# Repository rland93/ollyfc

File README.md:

# ollyfc
A small rust-embedded flight computer. RTIC, FrSky protocols, and STM32F4 hardware.

Board bring-up progress:

- [x] Buzzer
- [x] HDC 1080 Humidity and Temperature Sensor
- [x] BMI088 IMU
- [x] PCA9865 PWM Controller
- [x] Servo Channels from 5v power rail
- [x] FrSky SBUS External Reciever
- [x] BMP388 Pressure Sensor
- [x] LIS3MDL Magnetometer
- [x] FrSky SBUS 
- [ ] U-blox NEO m8n GPS unit
- [ ] NPA 730B differential pressure sensor
- [x] W25Q External Flash Memory
- [ ] UART for holybro 915MHz telemetry radio

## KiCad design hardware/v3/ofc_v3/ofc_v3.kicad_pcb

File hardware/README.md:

# OllyFC Hardware

We have hardware!

Schematics:

+ [V1 Schematic (PDF Link)](v1/ollyfc_v1_schematic.pdf)

# v1

V1 is manufactured by JLCPCB. The final project files (including JLCPCB Part Numbers / Bill of Materials) is in the v1/production folder. Images:

3D View (Tilted)

3D View (Top)

Traces (Top)

Traces (Bottom)

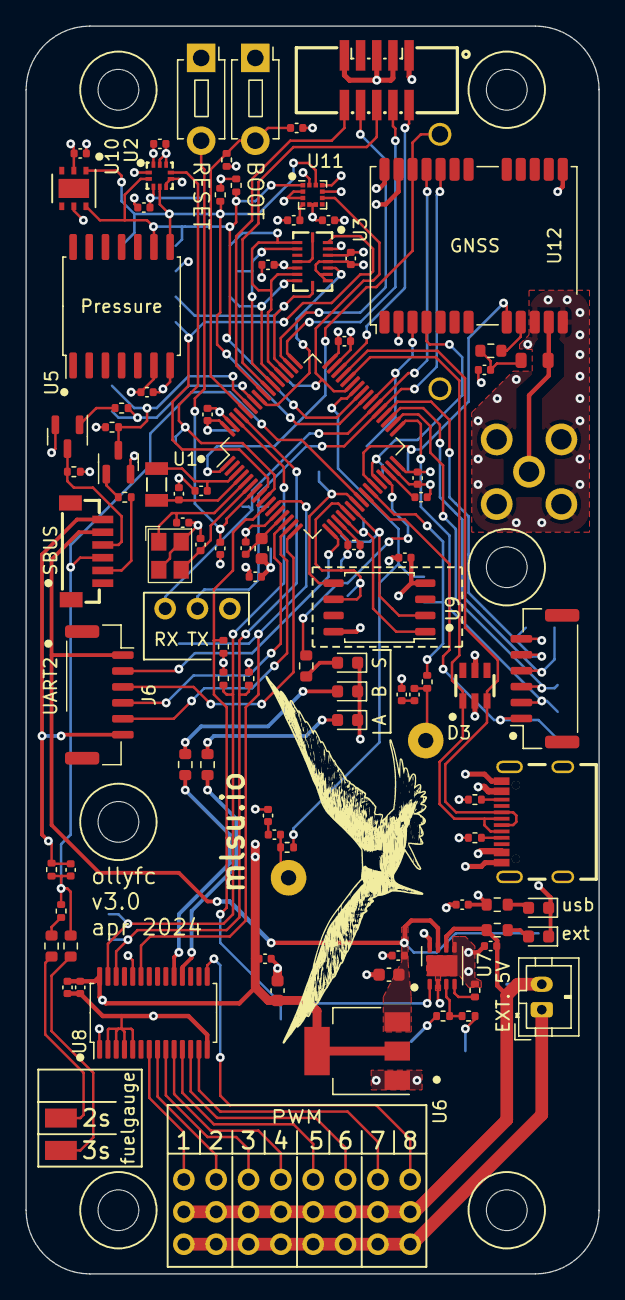
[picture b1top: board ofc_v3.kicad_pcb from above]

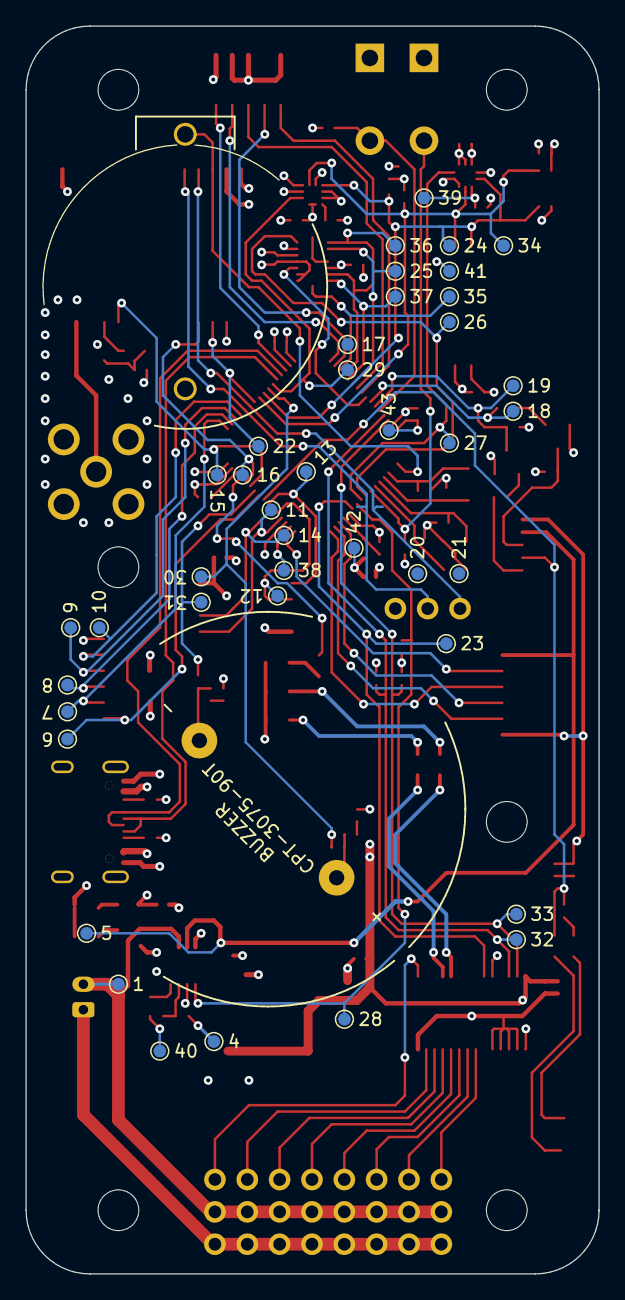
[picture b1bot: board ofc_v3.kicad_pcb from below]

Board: 4 copper layers, 45.0 x 98.0 mm, 150 parts (43 on the bottom side), 94 nets.

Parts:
BT1: 2998; BH-25C-1_ADM
BZ1: 102-CPT-3075-90T-ND; XDCR_CPT-3075-90T
C1, C2, C3, C4, C5, C8, C9, C11, C12, C13, C14, C15, C16, C19, C20, C22, C23, C24, C27, C28, C29, C30, C31, C32, C35, C36: 100n; C_0402_1005Metric
C6, C7: 10p; C_0402_1005Metric
C10, C21, C33: 4.7u; C_0402_1005Metric
C17, C18: 4.7u; C_0603_1608Metric
C25, C26: 33p; C_0402_1005Metric
C34: 10n; C_0402_1005Metric
CN1: 20021521-00010T1LF; IDC-SMD_10P-P1.27_X1270WVS-2X05B-6TV01
CN2: BM06B-SRSS-TBT(LF)(SN); CONN-SMD_BM06B-SRSS-TBT-LF-SN
D1, D7: 19-213/Y2C-CQ2R2L/3T(CY); LED_0603_1608Metric
D2, D4, D6: KT-0603R; LED_0603_1608Metric
D3: SRV05-4_C7420376; SOT-23-6_L2.9-W1.6-P0.95-LS2.8-BL-1
FB1: GZ1608D601TF; L_0603_1608Metric
H1, H2, H3, H4, H5, H6: DIN912; MountingHole_3.2mm_M3
J1: Conn_01x02; JST_PH_B2B-PH-K_1x02_P2.00mm_Vertical
J2, J3, J4: Conn_01x09; PinHeader_1x08_P2.54mm_Vertical
J5: GNSS_RF; SMA-TH_KH-SMA-KE-Z
J6, J7: Conn_01x06; JST_GH_SM06B-GHS-TB_1x06-1MP_P1.25mm_Horizontal
J8: Conn_01x03; PinHeader_1x03_P2.54mm_Vertical
L1: 27nH; L_0805_2012Metric
Q2, Q3: MMBT3904; SOT-23
R1, R2, R3, R4, R6, R12, R13, R14, R15, R16, R17, R25: 5.1K; R_0402_1005Metric
R5, R9, R24, R26, R27: 150; R_0603_1608Metric
R7, R8, R18, R19: 1.5K; R_0402_1005Metric
R10, R11, R21: 1K; R_0402_1005Metric
R20: 3K; R_0603_1608Metric
R22: 10; R_0603_1608Metric
R23: 7.5K; R_0603_1608Metric
SW1, SW2: SW_RST; SW_PUSH_1P1T_6x3.5mm_H4.3_APEM_MJTP1243
TP1, TP4, TP5, TP6, TP7, TP8, TP9, TP10, TP11, TP12, TP13, TP14, TP15, TP16, TP17, TP18, TP19, TP20, TP21, TP22, TP23, TP24, TP25, TP26, TP27, TP28, TP29, TP30, TP31, TP32, TP33, TP34, TP35, TP36, TP37, TP38, TP39, TP40, TP41, TP42, TP43: TestPoint; TestPoint_Pad_D1.0mm
TP2, TP3: TestPoint; TestPoint_Pad_2.0x2.0mm
U1: STM32F401RCTx; LQFP-64_10x10mm_P0.5mm
U2: BMP388; SENSORM-SMD_BMP388
U3: BMI088; LGA-16_L4.5-W3.0-P0.50-BL
U4: GT-USB-7010ASV; USB-C-SMD_G-SWITCH_GT-USB-7010ASV
U5: NPA-730B-10WD; SOIC-14W_7.5x9mm_P1.27mm
U6: AMS1117-3.3; SOT-223
U7: TPS2113ADRBR; VSON-8-1EP_3x3mm_P0.65mm_EP1.65x2.4mm
U8: PCA9685PW; TSSOP-28_4.4x9.7mm_P0.65mm
U9: W25Q128JVS; SOIC-8_5.23x5.23mm_P1.27mm
U10: HDC1080; Texas_PWSON-N6
U11: LIS3MDL; LGA-12_2x2mm_P0.5mm
U12: NEO-M8N; ublox_NEO
X1: X322512MSB4SI; OSC-SMD_4P-L3.2-W2.5-BL
X2: Q13FC1350000400; FC-135R_L3.2-W1.5

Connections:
5VIN: C17.1, C35.1, CN2.5, J6.1, TP5.1, U6.3 (VIN), U7.7 (OUT)
+3.3VA: C9.1, FB1.2, U1.13 (VREF+)
+3V3: C1.1, C2.1, C3.1, C4.1, C8.2, C10.1, C11.1, C12.1, C13.1, C14.1, C15.1, C18.1, C21.1, C22.1, C23.1, C27.1, C28.1, C36.1, CN1.1, FB1.1, R1.2, R2.2, R6.1, R12.2, R13.2, R14.2, R17.2, SW2.1, TP41.1, TP42.1, TP43.1, U1.19 (VDD), U1.32 (VDD), U1.48 (VDD), U1.64 (VDD), U2.1 (VDDIO), U2.5 (SDO), U2.6 (CSB), U2.10 (VDD), U3.3 (VDD), U3.11 (VDDIO), U5.7 (VDD), U6.2 (VOUT), U6.4 (VOUT), U8.1 (A0), U8.28 (VDD), U9.8 (VCC), U10.5 (VCC), U11.5 (Vdd), U11.6 (Vdd_IO), U11.10 (~CS), U12.2 (D_SEL), U12.23 (VCC)
/STATUS_LED: R24.1, U1.29 (PB10)
/io-sensors/2s: R20.1, TP2.1
/io-sensors/3s: R23.1, TP3.1
/io-sensors/rf_in: J5.1 (In), L1.2, U12.11 (RF_IN)
/io-sensors/s_port: CN2.4, Q2.3 (C), R14.1
/io-sensors/sbus_out: CN2.2, R16.2
/io-sensors/vcc_rf: R22.2, U12.9 (VCC_RF)
/power/ILIM: R10.1, U7.4 (ILIM)
/power/LED1: R26.1, U8.18 (LED11)
/power/LED2: R27.1, U8.19 (LED12)
/power/VSNS: R7.2, R8.1, U7.3 (VSNS)
/power/ch1: J2.1, U8.7 (LED1)
/power/ch2: J2.2, U8.8 (LED2)
/power/ch3: J2.3, U8.9 (LED3)
/power/ch4: J2.4, U8.10 (LED4)
/power/ch5: J2.5, U8.11 (LED5)
/power/ch6: J2.6, U8.12 (LED6)
/power/ch7: J2.7, U8.13 (LED7)
/power/ch8: J2.8, U8.15 (LED8)
ACC_CS: TP25.1, U1.54 (PD2), U3.14 (CSB1)
AIN_2: C24.1, CN2.3, R18.2, R19.1, R23.2, U1.24 (PC4)
AUX: J7.1, TP6.1, U1.25 (PC5)
BOOT0: C8.1, R25.2, SW2.2, U1.60 (BOOT0)
BUZZ+: R11.1, TP30.1, U1.42 (PA9)
BUZZ-: R21.1, TP31.1, U1.26 (PB0)
GND: BT1.2 (-), C1.2, C2.2, C3.2, C4.2, C5.2, C6.1, C7.1, C9.2, C10.2, C11.2, C12.2, C13.2, C14.2, C15.2, C16.2, C17.2, C18.2, C19.2, C21.2, C22.2, C23.2, C24.2, C25.1, C26.1, C27.2, C28.2, C29.2, C30.2, C32.2, C33.2, C34.2, C35.2, C36.2, CN1.3, CN1.5, CN1.9, CN2.6, D1.1 (K), D2.1 (K), D3.2, D4.1 (K), D6.1 (K), D7.1 (K), J1.1, J4.1, J4.2, J4.3, J4.4, J4.5, J4.6, J4.7, J4.8, J5.2 (Ext), J6.6, J7.6, J8.1, Q2.2 (E), Q3.2 (E), R3.1, R4.1, R8.2, R10.2, R19.2, R25.1, SW1.1, TP38.1, TP39.1, TP40.1, U1.12 (VSSA), U1.18 (VSS), U1.31 (VSS), U1.47 (VSS), U1.63 (VSS), U2.3 (VSS), U2.8 (VSS), U2.9 (VSS), U3.2 (NC), U3.4 (GNDA), U3.6 (GNDIO), U3.7 (PS), U4.1 (SHELL), U4.2 (SHELL), U4.3 (SHELL), U4.4 (SHELL), U4.A1B12 (GND), U4.B1A12 (GND), U5.6 (VSS), U6.1 (GND), U7.2 (~EN), U7.5 (GND), U7.9 (EP), U8.2 (A1), U8.3 (A2), U8.4 (A3), U8.5 (A4), U8.14 (VSS), U8.24 (A5), U9.4 (GND), U10.2 (GND), U11.2 (GND), U11.3 (GND), U11.9 (SDO/SA1), U11.12 (GND), U12.10 (GND), U12.12 (GND), U12.13 (GND), U12.24 (GND), X1.2 (GND), X1.4 (GND)
GNSS_INT: TP16.1, U1.28 (PB2), U12.4 (EXTINT)
GNSS_RESET: TP15.1, U1.27 (PB1), U12.8 (~RESET)
GYRO_CS: TP17.1, U1.57 (PB5), U3.5 (CSB2)
HSE_IN: C7.2, U1.5 (PH0), X1.1 (OSC1)
HSE_OUT: C6.2, U1.6 (PH1), X1.3 (OSC2)
I2C1_SCL: R12.1, TP32.1, U1.61 (PB8), U8.26 (SCL)
I2C1_SDA: R13.1, TP33.1, U1.62 (PB9), U8.27 (SDA)
I2C3_SCL: R2.1, TP24.1, U1.41 (PA8), U2.2 (SCK), U5.9 (SCL), U10.6 (SCL), U11.1 (SCL/SPC)
I2C3_SDA: R1.1, TP34.1, U1.40 (PC9), U2.4 (SDI), U5.8 (SCL), U10.1 (SDA), U11.11 (SDA/SDI/SDO)
IMU_DRDY: TP26.1, U1.8 (PC0), U3.1 (INT2)
JTCK_SWCLK: CN1.4, U1.49 (PA14)
JTDI: CN1.8, U1.50 (PA15)
JTDO_SWO: CN1.6, U1.55 (PB3)
JTMS_SWDIO: CN1.2, U1.46 (PA13)
JTRST: CN1.10, U1.56 (PB4)
MAG_DRDY: TP29.1, U1.43 (PA10), U11.8 (DRDY)
NRST: C5.1, SW1.2, U1.7 (NRST)
unnamed: BZ1.N, C31.1, R21.2
unnamed: BZ1.P, C20.1, R11.2
unnamed: C20.2, C30.1
unnamed: C31.2, C32.1
unnamed: C34.1, L1.1, R22.1
unnamed: D1.2 (A), R9.2
unnamed: D2.2 (A), R5.2
unnamed: D4.2 (A), R24.2
unnamed: D6.2 (A), R27.2
unnamed: D7.2 (A), R26.2
unnamed: Q2.1 (B), R15.2
unnamed: Q3.1 (B), R16.1
unnamed: R18.1, R20.2
unnamed: C26.2, U1.3 (PC14), X2.1
unnamed: C25.2, U1.4 (PC15), X2.2
unnamed: C33.1, U1.30 (VCAP1)
unnamed: U3.12 (INT3), U3.16 (INT1)
unnamed: R3.2, U4.A5 (CC1)
unnamed: R4.2, U4.B5 (CC2)
unnamed: C29.1, U11.4 (C1)
PRES_DRDY: TP27.1, U1.9 (PC1), U2.7 (INT)
PWR_STATE: R6.2, TP28.1, U1.10 (PC2), U7.1 (STAT)
SERVO_EN: TP23.1, U1.11 (PC3), U8.23 (~OE)
SPI1_MISO: TP14.1, U1.22 (PA6), U9.2 (DO(IO1))
SPI1_MOSI: TP13.1, U1.23 (PA7), U9.5 (DI(IO0))
SPI1_NSS: TP11.1, U1.20 (PA4), U9.1 (~CS)
SPI1_SCK: TP12.1, U1.21 (PA5), U9.6 (CLK)
SPI2_MISO: J7.4, TP9.1, U1.35 (PB14)
SPI2_MOSI: J7.5, TP10.1, U1.36 (PB15)
SPI2_NSS: J7.2, TP7.1, U1.33 (PB12)
SPI2_SCK: J7.3, TP8.1, U1.34 (PB13)
SPI3_MISO: TP36.1, U1.52 (PC11), U3.10 (SDO2), U3.15 (SDO1)
SPI3_MOSI: TP37.1, U1.53 (PC12), U3.9 (SDA/SDI)
SPI3_SCK: TP35.1, U1.51 (PC10), U3.8 (SCL/SCK)
TIMEPULSE: TP22.1, U1.39 (PC8), U12.3 (TIMEPULSE)
USART1_RX: Q3.3 (C), R17.1, TP19.1, U1.59 (PB7)
USART1_TX: R15.1, TP18.1, U1.58 (PB6)
USART2_CTS: J6.4, U1.14 (PA0)
USART2_RTS: J6.5, U1.15 (PA1)
USART2_RX: J6.2, U1.17 (PA3)
USART2_TX: J6.3, U1.16 (PA2)
USART6_RX: J8.3, TP21.1, U1.38 (PC7), U12.21 (RXD/SPI_MOSI)
USART6_TX: J8.2, TP20.1, U1.37 (PC6), U12.20 (TXD/SPI_MISO)
USBD+: D3.3, U1.45 (PA12), U4.A6 (DP1), U4.B6 (DP2)
USBD-: D3.1, U1.44 (PA11), U4.A7 (DN1), U4.B7 (DN2)
VBAT: BT1.1 (+), U1.1 (VBAT), U12.22 (V_BCKP)
VBUS: C16.1, D3.5, R5.1, R7.1, TP4.1, U4.A4B9 (VBUS), U4.B4A9 (VBUS), U7.8 (IN1)
VIN_EXT: C19.1, J1.2, J3.1, J3.2, J3.3, J3.4, J3.5, J3.6, J3.7, J3.8, R9.1, TP1.1, U7.6 (IN2)

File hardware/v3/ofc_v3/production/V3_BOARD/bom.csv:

Designator,Footprint,Quantity,Value,LCSC Part #
BT1,BH-25C-1_ADM,1,2998,DNP
BZ1,XDCR_CPT-3075-90T,1,102-CPT-3075-90T-ND,DNP
"C1, C11, C12, C13, C14, C15, C16, C19, C2, C20, C22, C23, C24, C27, C28, C29, C3, C30, C31, C32, C35, C36, C4, C5, C8, C9",0402,26,100n,C1525
"C10, C21, C33",0402,3,4.7u,C23733
"C17, C18",0603,2,4.7u,C19666
"C25, C26",0402,2,33p,C1562
C34,0402,1,10n,C15195
"C6, C7",0402,2,10p,C32949
CN1,IDC-SMD_10P-P1.27_X1270WVS-2X05B-6TV01,1,20021521-00010T1LF,C2972785
CN2,CONN-SMD_BM06B-SRSS-TBT-LF-SN,1,BM06B-SRSS-TBT(LF)(SN),C495540
"D1, D7",0603,2,19-213/Y2C-CQ2R2L/3T(CY),C72038
"D2, D4, D6",0603,3,KT-0603R,C2286
D3,SOT-23-6_L2.9-W1.6-P0.95-LS2.8-BL-1,1,SRV05-4_C7420376,C7420376
FB1,0603,1,GZ1608D601TF,C1002
"H1, H2, H3, H4, H5, H6",MountingHole_3.2mm_M3,6,DIN912,DNP
J1,JST_PH_B2B-PH-K_1x02_P2.00mm_Vertical,1,Conn_01x02,DNP
"J2, J3, J4",PinHeader_1x08_P2.54mm_Vertical,3,Conn_01x09,DNP
J5,SMA-TH_KH-SMA-KE-Z,1,GNSS_RF,DNP
"J6, J7",JST_GH_SM06B-GHS-TB_1x06-1MP_P1.25mm_Horizontal,2,Conn_01x06,C133065
J8,PinHeader_1x03_P2.54mm_Vertical,1,Conn_01x03,DNP
L1,0805,1,27nH,C98992
"Q2, Q3",SOT-23,2,MMBT3904,C20526
"R1, R12, R13, R2, R25, R3, R4, R6",0402,8,5.1K,C25905
"R10, R11, R21",0402,3,1K,C11702
"R14, R15, R16, R17",0402,4,5.1K,C25905
"R18, R19",0402,2,1.5K,C25867
R20,0603,1,3K,C4211
R22,0603,1,10,C22859
R23,0603,1,7.5K,C23234
"R24, R26, R27, R5, R9",0603,5,150,C22808
"R7, R8",0402,2,1.5K,C25867
"SW1, SW2",SW_PUSH_1P1T_6x3.5mm_H4.3_APEM_MJTP1243,2,SW_RST,DNP
"TP1, TP10, TP11, TP12, TP13, TP14, TP15, TP16, TP17, TP18, TP19, TP20, TP21, TP22, TP23, TP24, TP25, TP26, TP27, TP28, TP29, TP30, TP31, TP32, TP33, TP34, TP35, TP36, TP37, TP38, TP39, TP4, TP40, TP41, TP42, TP43, TP5, TP6, TP7, TP8, TP9",TestPoint_Pad_D1.0mm,41,TestPoint,
"TP2, TP3",TestPoint_Pad_2.0x2.0mm,2,TestPoint,DNP
U1,LQFP-64_10x10mm_P0.5mm,1,STM32F401RCTx,C74524
U10,Texas_PWSON-N6,1,HDC1080,C82227
U11,LGA-12_2x2mm_P0.5mm,1,LIS3MDL,C478483
U12,ublox_NEO,1,NEO-M8N,DNP
U2,SENSORM-SMD_BMP388,1,BMP388,C779278
U3,LGA-16_L4.5-W3.0-P0.50-BL,1,BMI088,C194919
U4,USB-C-SMD_G-SWITCH_GT-USB-7010ASV,1,GT-USB-7010ASV,C2988369
U5,SOIC-14W_7.5x9mm_P1.27mm,1,NPA-730B-10WD,DNP
U6,SOT-223,1,AMS1117-3.3,C6186
U7,VSON-8-1EP_3x3mm_P0.65mm_EP1.65x2.4mm,1,TPS2113ADRBR,C354512
U8,TSSOP-28_4.4x9.7mm_P0.65mm,1,PCA9685PW,C2678753
U9,SOIC-8_5.23x5.23mm_P1.27mm,1,W25Q128JVS,DNP
X1,OSC-SMD_4P-L3.2-W2.5-BL,1,X322512MSB4SI,C9002
X2,FC-135R_L3.2-W1.5,1,Q13FC1350000400,C32346

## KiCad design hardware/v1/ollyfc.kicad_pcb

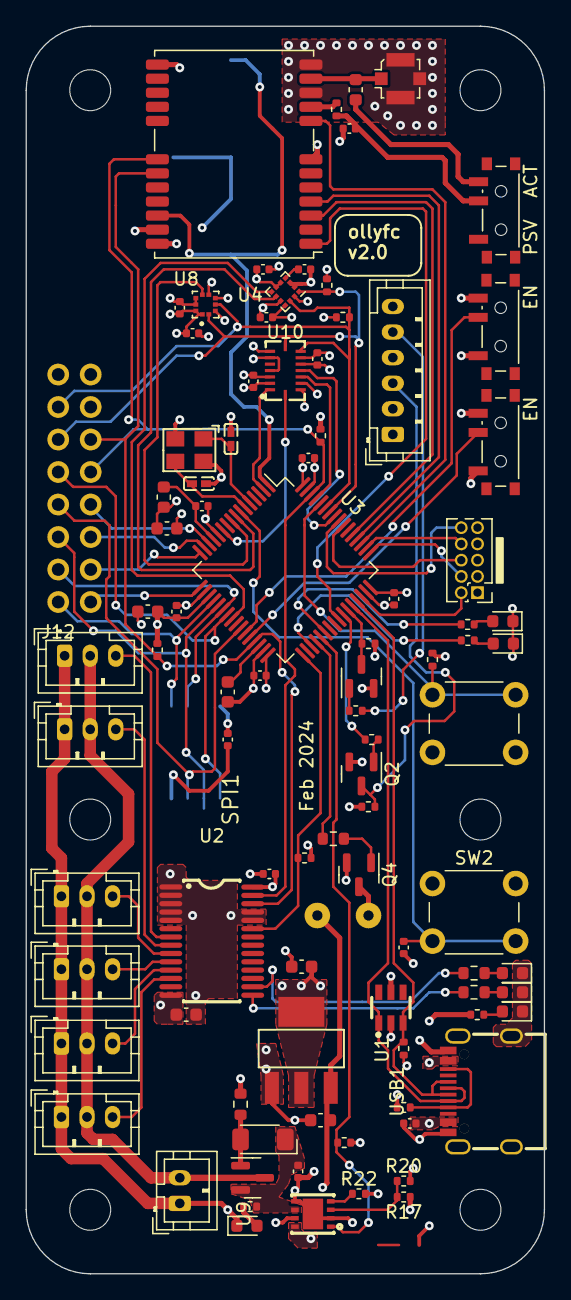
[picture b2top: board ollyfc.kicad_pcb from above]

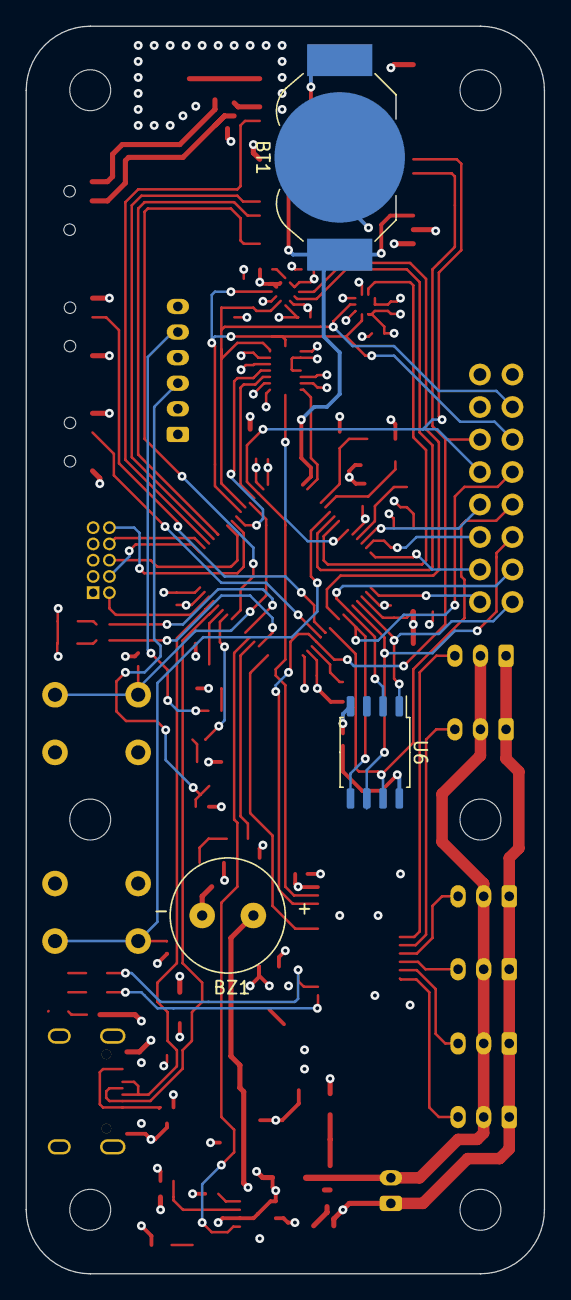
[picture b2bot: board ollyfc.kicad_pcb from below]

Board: 4 copper layers, 40.5 x 97.5 mm, 101 parts (3 on the bottom side), 82 nets.

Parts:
BT1: Battery_Cell; BatteryHolder_LINX_BAT-HLD-012-SMT
BZ1: CMT-9648-85T; XDCR_CMT-9648-85T
C1, C7, C8, C18, C19, C23: 4u7; C_0603_1608Metric
C2, C3, C4, C5, C6, C11, C12, C13, C14, C15, C16, C17, C20, C21, C24, C25: 100n; C_0402_1005Metric
C9, C10: 12pF; C0402
C22: 1u; C_0402_1005Metric
C26: 10n; C_0402_1005Metric
D1, D3, D4, D6: STATUS; LED_0603_1608Metric
D2: EXT_PWR_IND; LED_0603_1608Metric
D5: ZMM5V6-M; D_MiniMELF
D7: USB_IND; LED_0603_1608Metric
D8: SRV05-4_C7420376; SOT-23-6_L2.9-W1.6-P0.95-LS2.8-BL-1
FB1: GZ1608D601TF; L_0603_1608Metric
H1, H2, H3, H4, H5, H6: MountingHole; MountingHole_3.2mm_M3
J1: Conn_01x06; JST_PH_B6B-PH-K_1x06_P2.00mm_Vertical
J2: Conn_01x02; JST_PH_B2B-PH-K_1x02_P2.00mm_Vertical
J3, J6, J7, J9, J10, J11: Conn_01x03; JST_PH_B3B-PH-K_1x03_P2.00mm_Vertical
J5: Conn_02x05_Odd_Even; PinHeader_2x05_P1.27mm_Vertical
J8: Conn_Coaxial; U.FL_Molex_MCRF_73412-0110_Vertical
J12: Conn_01x08; PinHeader_1x08_P2.54mm_Vertical
J13: Conn_01x04; PinHeader_1x08_P2.54mm_Vertical
L1: L_Small; L_0603_1608Metric
Q1: AO3401A; SOT-23
Q2, Q3, Q4: MMBT3904; SOT-23
R1, R2, R3, R4, R5, R8, R9, R12, R15, R21, R23, R25: 5K1; R_0402_1005Metric
R6, R7, R10, R11, R16, R17, R20: 1K5; R_0402_1005Metric
R13, R14, R18, R26: 680; R_0603_1608Metric
R19: 10; R_0402_1005Metric
R22: 680; R_0402_1005Metric
SW2, SW3: SW_Push; SW_PUSH_6mm
SW4, SW5, SW6: MODE1; SW_SPDT_PCM12
U1: AMS1117-3.3; SOT-223-3_L6.5-W3.4-P2.30-LS7.0-BR
U2: PCA9685PW,118; TSSOP-28_L9.7-W4.4-P0.65-LS6.4-TL
U3: STM32F411RETx; LQFP-64_10x10mm_P0.5mm
U4: LIS3MDL; LGA-12_2x2mm_P0.5mm
U6: W25Q128JVS; SOIC-8_5.23x5.23mm_P1.27mm
U7: BMP388; BoschSensortec-BMP-388_PQFN50P200X200X80-10N
U8: NEO-M8N; ublox_NEO
U9: TPS2113ADRBR; SON-8_L3.0-W3.0-P0.65-LS3.0-BL-EP
U10: BMI088; LGA-16_L4.5-W3.0-P0.50-BL
USB1: USB-TYPE-C-018; USB-C_SMD-TYPE-C-31-M-12
X1: X322516MLB4SI; OSC-SMD_4P-L3.2-W2.5-BL

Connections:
5VIN: BZ1.P (-), C23.1, U1.3 (VIN), U9.7 (OUT)
+3.3VA: C6.1, FB1.1, U3.13 (VDDA)
+3V3: C1.1, C2.1, C3.1, C4.1, C5.1, C7.1, C12.1, C13.1, C14.1, C15.1, C16.2, C17.1, C18.1, C19.1, C21.1, C22.1, FB1.2, J1.2, J5.1, J13.1, R1.1, R4.2, R5.2, R7.1, R8.1, R9.1, R12.1, R25.1, SW3.2, SW4.3 (C), SW5.3 (C), U1.2 (VOUT), U1.4 (VOUT), U2.14 (VSS), U2.28 (VDD), U3.19 (VDD), U3.32 (VDD), U3.48 (VDD), U3.64 (VDD), U4.5 (Vdd), U4.6 (Vdd_IO), U4.10 (~CS), U6.8 (VCC), U7.1 (VDDIO), U7.6 (CSB), U7.10 (VDD), U8.23 (VCC), U10.3 (VDD), U10.7 (PS), U10.11 (VDDIO), U10.14 (CSB1)
/HSE_IN: C9.1, U3.5 (PH0), X1.1 (OSC1)
/HSE_OUT: C10.1, U3.6 (PH1), X1.3 (OSC2)
/IO/RF_IN: J8.1 (In), L1.2, U8.11 (RF_IN)
/IO/SERVO_CH1: J3.3, U2.7 (LED1)
/IO/SERVO_CH2: J6.3, U2.8 (LED2)
/IO/SERVO_CH3: J7.3, U2.9 (LED3)
/IO/SERVO_CH4: J9.3, U2.10 (LED4)
/IO/SERVO_CH5: J10.3, U2.11 (LED5)
/IO/SERVO_CH6: J11.3, U2.12 (LED6)
/Power/ILIM: R22.1, U9.4 (ILIM)
/Power/VSNS: R17.2, R20.1, U9.3 (VSNS)
/SBUS_OUT: J1.5, R3.1
/S_PORT: J1.3, Q2.3 (C), R4.1
ACCEL_INT1: U3.11 (PC3), U10.16 (INT1)
ACCEL_INT2: U3.2 (PC13), U10.1 (INT2)
BOOT0: R15.2, SW3.1, U3.60 (BOOT0)
BUZZER: R26.1, U3.36 (PB15)
FMEM_CS: J12.1, U3.20 (PA4), U6.1 (~CS)
FMEM_HOLD: J12.4, U3.26 (PB0), U6.7 (IO3)
GND: BT1.2 (-), C1.2, C2.2, C3.2, C4.2, C5.2, C6.2, C7.2, C8.2, C9.2, C10.2, C11.1, C12.2, C13.2, C14.2, C15.2, C16.1, C17.2, C18.2, C19.2, C20.2, C21.2, C22.2, C23.2, C24.2, C25.2, C26.2, D1.1 (K), D2.1 (K), D3.1 (K), D4.1 (K), D6.1 (K), D7.1 (K), D8.2, J1.1, J2.1, J3.1, J5.3, J5.5, J5.9, J6.1, J7.1, J8.2 (Ext), J9.1, J10.1, J11.1, J12.8, Q2.2 (E), Q3.2 (E), Q4.2 (E), R15.1, R18.2, R20.2, R21.2, R22.2, R23.2, SW2.1, SW4.1 (A), SW5.1 (A), U1.1 (GND), U2.1 (A0), U2.2 (A1), U2.3 (A2), U2.4 (A3), U2.5 (A4), U2.24 (A5), U2.25 (EXTCLK), U3.12 (VSSA), U3.18 (VSS), U3.31 (VSS), U3.47 (VSS), U3.63 (VSS), U4.2 (GND), U4.3 (GND), U4.9 (SDO/SA1), U4.12 (GND), U6.4 (GND), U7.3 (VSS), U7.5 (SDO), U7.8 (VSS), U7.9 (VSS), U8.7 (VDD_USB), U8.10 (GND), U8.12 (GND), U8.13 (GND), U8.24 (GND), U9.2 (~EN), U9.5 (GND), U9.9 (EP), U10.2 (NC), U10.4 (GNDA), U10.6 (GNDIO), U10.10 (SDO2), U10.15 (SDO1), USB1.0 (SH), USB1.2 (SH), USB1.3 (SH), USB1.A1 (GND), USB1.A12 (GND), USB1.B1 (GND), USB1.B12 (GND), X1.2 (GND), X1.4 (GND)
GNSS_INT: U3.52 (PC11), U8.4 (EXTINT)
GNSS_RESET: U3.51 (PC10), U8.8 (~RESET)
GNSS_SAFEBOOT: U3.41 (PA8), U8.1 (~SAFEBOOT)
GNSS_TIMEP: U3.53 (PC12), U8.3 (TIMEPULSE)
GYRO_INT3: U3.57 (PB5), U10.12 (INT3)
GYRO_INT4: U3.61 (PB8), U10.13 (INT4)
I2C1_SCL: J12.6, R12.2, U3.58 (PB6), U4.1 (SCL/SPC), U7.2 (SCK), U10.8 (SCL/SCK)
I2C1_SDA: J12.7, R1.2, U3.59 (PB7), U4.11 (SDA/SDI/SDO), U7.4 (SDI), U10.9 (SDA/SDI)
I2C2_SCL: J13.3, R9.2, U2.26 (SCL), U3.29 (PB10), U8.19 (SCL/SPI_CLK)
I2C2_SDA: J13.4, R8.2, U2.27 (SDA), U3.62 (PB9), U8.18 (SDA/~SPI_CS)
JTCK_SWCLK: J5.4, U3.49 (PA14)
JTDI: J5.8, U3.50 (PA15)
JTDO_SWO: J5.6, U3.55 (PB3)
JTMS_SWDIO: J5.2, U3.46 (PA13)
JTRST: J5.10, U3.56 (PB4)
LED1: R6.1, U3.38 (PC7)
LED2: R10.1, U3.35 (PB14)
MAG_DRDY: U3.8 (PC0), U4.8 (DRDY)
MAG_INT: U3.24 (PC4), U4.7 (INT)
MODE1: SW4.2 (B), U3.27 (PB1)
MODE2: SW5.2 (B), U3.28 (PB2)
NRST: C11.2, SW2.2, U3.7 (NRST)
unnamed: BZ1.N (+), Q4.3 (C)
unnamed: D1.2 (A), R6.2
unnamed: D2.2 (A), R16.2
unnamed: D3.2 (A), R10.2
unnamed: D4.2 (A), R13.2
unnamed: D5.2 (A), Q1.1 (G), R18.1
unnamed: D6.2 (A), R14.2
unnamed: D7.2 (A), R11.2
unnamed: Q2.1 (B), R2.2
unnamed: Q3.1 (B), R3.2
unnamed: Q4.1 (B), R26.2
unnamed: C26.1, R19.2, SW6.2 (B)
unnamed: L1.1, SW6.3 (C)
unnamed: C8.1, U3.30 (VCAP1)
unnamed: C20.1, U4.4 (C1)
unnamed: R19.1, U8.9 (VCC_RF)
PRES_INT: U3.9 (PC1), U7.7 (INT)
PWM_EN: R23.1, U2.23 (~OE), U3.33 (PB12)
PWR_STATE: R25.2, U3.37 (PC6), U9.1 (STAT)
SPI1_MISO: J12.2, U3.22 (PA6), U6.2 (DO(IO1))
SPI1_MOSI: J12.5, U3.23 (PA7), U6.5 (DI(IO0))
SPI1_SCK: J12.3, U3.21 (PA5), U6.6 (CLK)
STATUS_A: R13.1, U2.15 (LED8)
STATUS_B: R14.1, U2.16 (LED9)
USART1_RX: Q3.3 (C), R5.1, U3.43 (PA10)
USART1_TX: R2.1, U3.42 (PA9)
USART2_CTS: J13.5, U3.14 (PA0)
USART2_RTS: J13.6, U3.15 (PA1)
USART2_RX: J13.8, U3.17 (PA3)
USART2_TX: J13.7, U3.16 (PA2)
USBCC: R21.1, USB1.A5 (CC1), USB1.B5 (CC2)
USBD+: D8.3, R7.2, U3.45 (PA12), USB1.A6 (DP1), USB1.B6 (DP2)
USBD-: D8.1, U3.44 (PA11), USB1.A7 (DN1), USB1.B7 (DN2)
VBAT: BT1.1 (+), U3.1 (VBAT), U8.22 (V_BCKP)
VBUS: C25.1, D8.5, R11.1, R17.1, U9.8 (IN1), USB1.A4 (VBUS), USB1.A9 (VBUS), USB1.B4 (VBUS), USB1.B9 (VBUS)
VIN: C24.1, D5.1 (K), Q1.2 (S), R16.1, U9.6 (IN2)
VIN_EXT: J2.2, J3.2, J6.2, J7.2, J9.2, J10.2, J11.2, Q1.3 (D)

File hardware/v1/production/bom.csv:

Designator,Footprint,Quantity,Value,LCSC Part #,
BT1,BAT-TH_MY-927-01,1,Battery_Cell,C964850,Extended
"C1, C18, C19, C21, C23, C7, C8",603,7,4u7,C19666,Basic
"C10, C9",402,2,10pF,C32949,Basic
"C11, C12, C13, C14, C15, C16, C17, C2, C22, C24, C25, C3, C4, C5, C6",402,15,100n,C1525,Basic 
"D1, D2, D3, D4, D6",603,5,STATUS,C2286,Basic
D5,D_MiniMELF,1,ZMM5V6-M,C8062,Basic
FB1,603,1,GZ1608D601TF,C1002,Basic
J4,USB_C_Receptacle_G-Switch_GT-USB-7010ASV,1,USB_C_Receptacle_USB2.0,C2988369,Extended
J5,PinHeader_2x05_P1.27mm_Vertical,1,Conn_02x05_Odd_Even,C7501289,Extended
Q1,SOT-23,1,AO3401A,C15127,Basic
"Q2, Q3, Q4",SOT-23,3,MMBT3904,C20526,Basic
"R1, R12, R17, R19, R2, R21, R25, R3, R4, R5, R8, R9",402,12,5K1,C25905,Basic
"R10, R11, R16, R23, R24, R6, R7",402,7,1K5,C25867,Basic
"R13, R14, R18, R22, R26",603,5,680,C23228,Basic
U1,SOT-223-3_TabPin2,1,AMS1117-3.3,C6186,Basic
U10,SOT-23-6,1,SRV05-4,C7420376,Extended
U2,QFN-28-1EP_6x6mm_P0.65mm_EP4.25x4.25mm,1,PCA9685BS,C5191634,Extended
U3,LQFP-64_10x10mm_P0.5mm,1,STM32F411RETx,C94355,Extended
U5,LGA-16_L4.5-W3.0-P0.50-BL,1,BMI088,C194919,Extended
U7,BoschSensortec-BMP-388_PQFN50P200X200X80-10N,1,BMP388,C779278,Extended
U9,TSSOP-8_4.4x3mm_P0.65mm,1,TPS2113APW,C130052,Extended
Y1,Crystal_SMD_SeikoEpson_TSX3225-4Pin_3.2x2.5mm,1,X322516MLB4SI,C13738,Basic

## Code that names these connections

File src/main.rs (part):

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
        // Flash memory
        let mem = mem_init(
            gpioa.pa4.into_push_pull_output(),
            gpioa.pa5.into_alternate(),
            gpioa.pa6.into_alternate(),
            gpioa.pa7.into_alternate(),
            dp.SPI1,
            dp.TIM1,
            &clocks,
        );

        // Gyroscope
        let mut mpu_int = gpiob.pb8.into_pull_down_input();
        let mpu = mpu_6050_init(
            &mut mpu_int,
            gpiob
                .pb6
                .into_alternate()
                .internal_pull_up(true)
                .set_open_drain(),
            gpiob
                .pb7
                .into_alternate()
                .internal_pull_up(true)
                .set_open_drain(),
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        let mut sbus_in: Rx<USART1, u8> = dp
            .USART1
            .rx(
                gpioa.pa10.into_alternate(),
                Config::default()
                    .baudrate(100_000.bps())
                    .dma(serial::config::DmaConfig::Rx),
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
        // Set up PWM
        info!("PWM...");
        let pwm = dp.TIM3.pwm_hz(Channel3::new(gpiob.pb0), 52.Hz(), &clocks);
        let mut elevator_channel = pwm.split();
        elevator_channel.enable();

        // USB -
        info!("USB Button Setup...");
        let usb_btn = gpioa.pa0.into_pull_up_input();
        // Wait for gpio setup
        util_timer.delay_ms(5u32);

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            usb_global: dp.OTG_FS_GLOBAL,
            usb_device: dp.OTG_FS_DEVICE,
            usb_pwrclk: dp.OTG_FS_PWRCLK,
            pin_dm: gpioa.pa11.into(),
            pin_dp: gpioa.pa12.into(),
            hclk: clocks.hclk(),
        };
        unsafe {
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
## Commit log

2023-12-09 fix compile issues with w25q
2023-12-09 W25q Memory Example
2023-12-09 flash storage driver and rtic main
2023-12-09 Flight logger
    The flight logger is designed to consume sensor and registered flight
    control inputs and write them to the built-in spi flash. The logging
    system is composed of two tasks: a log collector task and a log writer
    task. The log collector collects log entries at a regular interval and
    adds them to a queue. The log writer task consumes the queue, packs the
    entries (32 bytes) into a flash page (256 bytes), and writes the page
2023-12-09 renamed to ollyfc
2023-12-09 Separated library logic from binary logic
2023-12-09 MPU6050 sensor
    Add task to handle storing of MPU6050 sensor data. Updated flight data
    type to be 64 bytes (up from 32 bytes) since we have 6 x 4 byte floats
    for accel x, y, z and gyro x, y, z.
2023-12-09 Fix interrupts for gyroscope
2023-12-09 Added interrupt for sensor task.
    Sensor task will now be triggered whenvever sensor recieves new data
    (1kHz).
2023-12-09 sbus read over DMA
2023-12-09 licensed MPL
2023-12-09 Encapsulate some tasks
2023-12-09 elevator control policy and primary flight task
2023-12-09 PWM, flight control module, and some reorg of
    - created a new module, flight_control, that will hold control code.
    - renamed flightlogger to flight_logger
    - added PWM module for control surfaces
    - changed hardware of w25q
    - removed some timers that were not used for anything
2023-12-09 Encapsulate some tasks to move them out of main.rs
2023-12-09 Encapsulate gyro setup logic
2023-12-09 i2c2->i2c1 for mpu6050
2023-12-09 Cargo.toml changes
2023-12-09 Cargo.toml cleanup & audit
2023-12-09 USB Bringup example program #2
2023-12-10 USB configuration #3 #2
    Brought USB configuration into the program. We added a button at A0 that
    controls what mode the system is in. If the button is pressed (grounded)
    then the system boots into USB mode. Otherwise, it boots into flight
    control mode.
    The USB device and serial device is instantiated no matter what, but if
    it sits idle this doesn't impact performance and makes it significantly
2023-12-10 Boot mode switch
2023-12-10 Moved into 2 separate cargo workspaces
2023-12-10 Removed workspace. Two separate applications.
2023-12-10 TUI for USB communication
2023-12-10 TUI tweaks
2023-12-10 Project reorganize
    Moved lots of things out of main and into their own modules.
2023-12-10 Move common types into separate crate #6
    Since we are accessing logs from both the TUI and the embedded software,
    we need to share the types between the two. This commit moves the types
    into a separate crate.
2023-12-10 USB module #17
2023-12-11 WIP Svelte application for host controller #16
    Partially implemented host application. Embedded USB driver. USB task for
    listening for data from host. Host side USB enumeration and search for matching
    FC device (by VID/PID). Hardcoded VID/PID used from pid.codes. Serial control on
    host and embedded side. Verified sending commands from host to embedded, but no
    bidirectional communication yet.
2023-12-11 Embedded USB serial receive/command dispatch
2023-12-11 Svelte + Tauri Gitignore #16
2023-12-12 App icon
2023-12-12 End-to-end IO #16
    It's still REALLY buggy and very slow.
2023-12-13 Singlethreaded USB #19
2023-12-13 More explicit handling of commands
2023-12-13 LogInfoPage type; impl display for Command type
2023-12-13 Flight logs attach timestamp
2023-12-13 Logging changes #5
    Refactored the logger a little bit. Logging is implemented (and tested...ish). Moved management of the W25Q flash into the logging module itself so that writes are more managed.
    Created FIFO queue system for logging. Logs are written to a bounded region which is set at initializtion. The first block is reserved. The size of the region is written to the first page of the firs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
2023-12-13 Command handler for get log data
2023-12-14 Style changes to Usb State area
2023-12-14 Readout logs from memory region
2023-12-14 More sensible no_std handling of common module
2023-12-14 GetFlash command
2023-12-14 update return type of flightlogdata from_bytes
2023-12-14 split out command parse from byte read logic
    added TS type for flight data
2023-12-14 rebase with next
2023-12-14 Write latest cursor. Improved mem err handler
2023-12-14 fix log info page buffer size issue
2023-12-14 download progress #24
    - log download now shows progress bar and logs/total
    - we also have a log info type that can be used to extract metadata, no ui for this yet
    - some work on #22 with log info type
    - changed in general the event types to be more consistent
2023-12-26 device IO display changes
2023-12-26 Created abstraction for protocol #28
    We are going to handle most/(maybe all?) USB serial writes through a
    protocol that will CRC and ack the data. This makes it more ergonomic
    (abstract the HAL calls) and more reliable (CRC). For details see the
    issue.
2023-12-27 Log read sequence
    Implemented log read sequence for host application. Sending the log read command to the device enters a special mode, "direct access", where we can read a page from the flash. We get the address boun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
2023-12-28 Fixed compilation warnings.
    I needed to create a no_sensors feature so that the board would boot when disconnected from the external peripherals (the Rx and the gyro). Fixed the issues I was having with those peripherals so it'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
2023-12-28 Add chart view
    save to CSV functionality
    improvements to serialization
    lots of small things
2023-12-29 Enable or disable logging #23
2024-01-19 Removed MPU6050. Made logging toggle-able.
2024-02-07 BMI160 sensor
2024-02-07 PCB KiCad Project. Schematics, board files, BOM
2024-02-08 very basic example
2024-02-11 some hardware designs
2024-02-14 Route another?
2024-02-18 v2 PCB design
2024-02-25 JLC part footprints
2024-03-09 v2 files
2024-03-09 files
2024-03-10 Update BMP388 dependency to use new driver
2024-03-10 New shared library
    The way I'm thinking we do this is that all of the application logic
    will be in a library that can be shared across multiple different
    hardware applications. Individual BBU tasks will be in "examples" that
    are able to be developed independently. So, starting with the pressure
    sensor, we have an example code that called bbu-bmp388.rs that will
    exercise all possible functions of the pressure sensor. Successful BBU
2024-03-10 #35 Bring-up example for pressure sensor
2024-03-10 #35 Add temp reading to example
2024-03-10 #35 bmp388 fix, clear interrupt on sensor side after read
2024-03-10 #39 lis3mdl sensor read in ISR
2024-03-27 Re-organize test points. Fix LED footprints #36
2024-03-27 ignore backup files
2024-03-27 #36 Fix short in PCA9865, Remove 'TP' silkscreens
2024-03-27 #36 Aux line
2024-03-27 Add aux line #36
2024-03-27 BMI088 example code
2024-03-27 remove unused in pressure.rs
2024-03-27 STM32F411 SVD
2024-04-02 v3 schematic + layout
2024-04-02 Added some organization to schematic
2024-04-10 dead-end board files
2024-04-10 add v3 board redesign
2024-04-17 Deleted old/irrelevant examples
2024-04-17 Add HDC1080 Example
2024-04-17 Add buzzer example
2024-04-17 Update board configuration
2024-04-21 PWM - LED and Servo control
2024-04-23 cleanup
2024-04-23 alphabetize modules (rustfmt)
2024-04-30 imu bring-up with interrupt config
2024-04-30 pwm bring-up example changes
2024-07-26 Add sbus example
2024-07-26 remove compiler warnings in pca9685 example
2024-07-26 add board schematic PDF for easy reference
2024-07-26 Add bringup progress to README
2024-07-26 remove outdated code in main
2024-07-26 simple USB CDC example code
2024-07-26 fix compilation warnings
2024-07-29 example for BMP388
2024-07-31 flash memory test
2024-07-31 USB protocol design and firmware for endpoint
2024-08-01 - common Message type with cross platform CRC - usb (firmware) configured as bulk transfer device - fixes to ollyfc_common which make it more readable for conditionally compiled parts - addition of .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
2024-08-03 USB and host application
2024-08-04 emphasis for compatible device in USB list
2024-08-04 fix compiler warnings in imu example
2024-08-04 fix compiler warnings in usb module
2024-08-05 status LED
2024-08-05 pin stm32f4xx-hal
2024-08-05 update pressure sensor example to show altitude
2024-08-05 added some tone definitions to buzzer example
2024-08-05 standardize hdc-1080 example code
2024-08-05 i2c test code for checking the i2c3 bus
2024-08-05 standardize clock setup, 64 MHz and use HSE for all examples
2024-08-05 LSE BBU example, raw xyz axis data
2024-08-06 combine examples in main.rs
2024-09-04 Fix warnings across the project, clean up lib
2024-09-04 add examples README.md
2024-09-04 sketch of logging system with a page cache.
